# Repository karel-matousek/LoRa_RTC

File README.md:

# LoRa_RTC
This project is a Bachelor's thesis in progress, which pertains to the development and design of a LoRaWAN Class-B beacon receiver. The goal of the device is to extract and decode the time information contained in the received message, display it using an OLED display, and generate a 1pps output signal.

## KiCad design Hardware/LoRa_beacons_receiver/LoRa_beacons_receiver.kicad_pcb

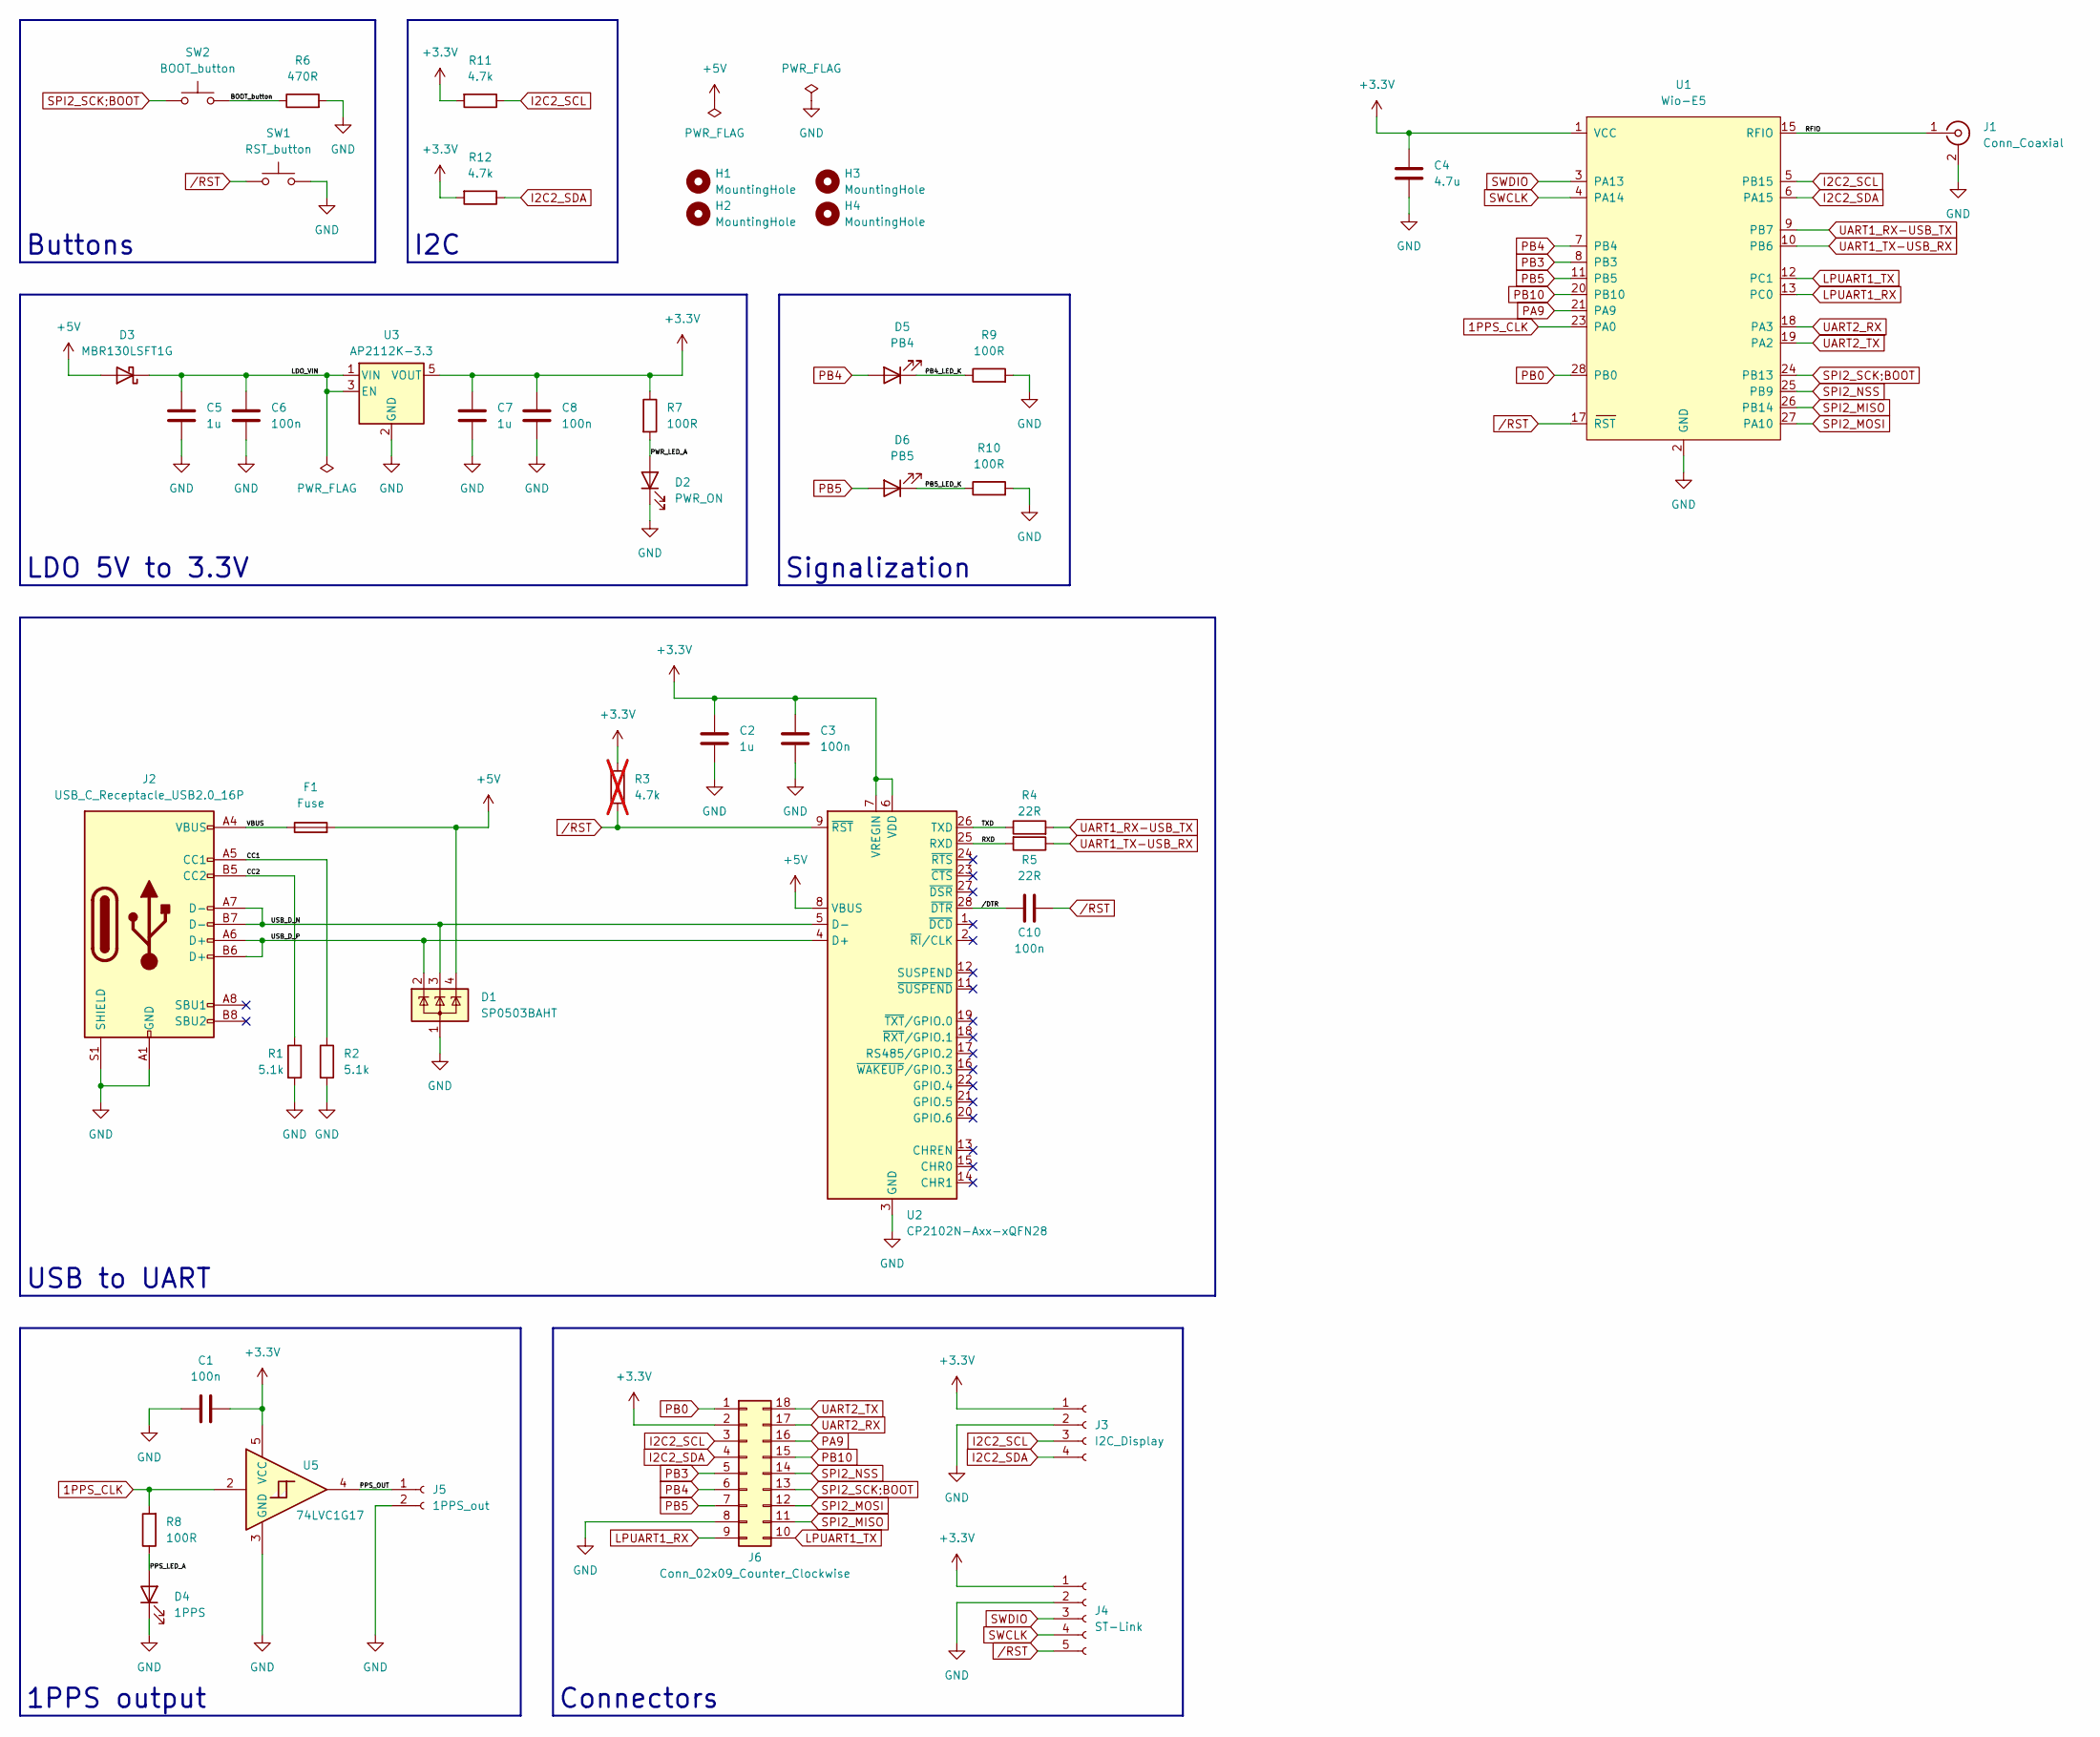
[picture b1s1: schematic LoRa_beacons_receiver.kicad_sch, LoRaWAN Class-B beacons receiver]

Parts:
C1, C3, C6, C8, C10: 100n; C_0805_2012Metric_Pad1.18x1.45mm_HandSolder; Manufacturer part number 08055C104JAT2A
C2, C5, C7: 1u; C_0805_2012Metric_Pad1.18x1.45mm_HandSolder; Manufacturer part number CC0805KKX7R7BB105
C4: 4.7u; C_0805_2012Metric_Pad1.18x1.45mm_HandSolder; Manufacturer part number TMK212AB7475KG-T
D1: SP0503BAHT; SOT-143; Manufacturer part number SP0503BAHTG-LF
D2: PWR_ON; LED_0805_2012Metric_Pad1.15x1.40mm_HandSolder; Manufacturer part number LTST-C171KRKT
D3: MBR130LSFT1G; SOD-123FL_l; Manufacturer part number MBR130LSFT1G
D4: 1PPS; LED_0805_2012Metric_Pad1.15x1.40mm_HandSolder; Manufacturer part number LTST-C171KRKT
D5: PB4; LED_0805_2012Metric_Pad1.15x1.40mm_HandSolder; Manufacturer part number LTST-C171KRKT
D6: PB5; LED_0805_2012Metric_Pad1.15x1.40mm_HandSolder; Manufacturer part number LTST-C171KRKT
F1: Fuse; Fuse_0603_1608Metric_Pad1.05x0.95mm_HandSolder; Manufacturer part number ERBRE1R00V
H1, H2, H3, H4: MountingHole; MountingHole_2.2mm_M2
J1: Conn_Coaxial; RF2-143-T-17-50-G_l; Manufacturer part number RF2-143-T-17-50-G
J2: USB_C_Receptacle_USB2.0_16P; USB_C_Receptacle_GCT_USB4105-xx-A_16P_TopMnt_Horizontal; Manufacturer part number USB4105-GF-A-120
J3: I2C_Display; PinSocket_1x04_P2.54mm_Vertical
J4: ST-Link; PinSocket_1x05_P2.54mm_Vertical; Manufacturer part number ZL262-5SG
J5: 1PPS_out; PinSocket_1x02_P2.54mm_Horizontal; Manufacturer part number ZL263-2SG
J6: Conn_02x09_Counter_Clockwise; PinSocket_2x09_P2.54mm_Vertical; Manufacturer part number ZL262-9SG
R1, R2: 5.1k; R_0805_2012Metric_Pad1.20x1.40mm_HandSolder; Manufacturer part number WR08X5101FTL
R3: 4.7k; R_0805_2012Metric_Pad1.20x1.40mm_HandSolder; Manufacturer part number CRCW08054K70FKTABC; not fitted
R4, R5: 22R; R_0805_2012Metric_Pad1.20x1.40mm_HandSolder; Manufacturer part number CRGH0805J22R
R6: 470R; R_0805_2012Metric_Pad1.20x1.40mm_HandSolder; Manufacturer part number ERJP06J471V
R7, R8, R9, R10: 100R; R_0805_2012Metric_Pad1.20x1.40mm_HandSolder; Manufacturer part number CRCW0805100RFKTABC
R11, R12: 4.7k; R_0805_2012Metric_Pad1.20x1.40mm_HandSolder; Manufacturer part number CRCW08054K70FKTABC
SW1: RST_button; SW_PUSH_6mm; Manufacturer part number TACT4101-11250-A
SW2: BOOT_button; SW_PUSH_6mm; Manufacturer part number TACT4101-11250-A
U1: Wio-E5; STM32WLE5JC_l
U2: CP2102N-Axx-xQFN28; QFN-28-1EP_5x5mm_P0.5mm_EP3.35x3.35mm; Manufacturer part number CP2102-GM
U3: AP2112K-3.3; SOT-23-5; Manufacturer part number AP2112K-3.3TRG1
U5: 74LVC1G17; SOT-23-5_HandSoldering; Manufacturer part number 74LVC1G17GV.125

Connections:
1PPS_CLK: R8.2, U1.23 (PA0), U5.2
+3.3V: C1.1, C2.1, C3.1, C4.1, C7.1, C8.1, J3.1, J4.1, J6.2, R3.1, R7.1, R11.2, R12.2, U1.1 (VCC), U2.6 (VDD), U2.7 (VREGIN), U3.5 (VOUT), U5.5 (VCC)
+5V: D1.4 (K), D3.2 (A), F1.2, U2.8 (VBUS)
/BOOT_button: R6.1, SW2.2
/CC1: J2.A5 (CC1), R2.1
/CC2: J2.B5 (CC2), R1.1
/LDO_VIN: C5.1, C6.1, D3.1 (K), U3.1 (VIN), U3.3 (EN)
/PB4_LED_K: D5.1 (K), R9.1
/PB5_LED_K: D6.1 (K), R10.1
/PPS_LED_A: D4.2 (A), R8.1
/PPS_OUT: J5.1, U5.4
/PWR_LED_A: D2.2 (A), R7.2
/RFIO: J1.1 (In), U1.15 (RFIO)
/RXD: R5.2, U2.25 (RXD)
/TXD: R4.1, U2.26 (TXD)
/USB_D_N: D1.3 (K), J2.A7 (D-), J2.B7 (D-), U2.5 (D-)
/USB_D_P: D1.2 (K), J2.A6 (D+), J2.B6 (D+), U2.4 (D+)
/VBUS: F1.1, J2.A4 (VBUS), J2.A9 (VBUS), J2.B4 (VBUS), J2.B9 (VBUS)
//DTR: C10.1, U2.28 (~DTR)
GND: C1.2, C2.2, C3.2, C4.2, C5.2, C6.2, C7.2, C8.2, D1.1 (A), D2.1 (K), D4.1 (K), J1.2 (Ext), J2.A1 (GND), J2.A12 (GND), J2.B1 (GND), J2.B12 (GND), J2.S1 (SHIELD), J3.2, J4.2, J5.2, J6.8, R1.2, R2.2, R6.2, R9.2, R10.2, SW1.2, U1.2 (GND), U1.14 (GND), U1.16 (GND), U1.22 (GND), U2.3 (GND), U2.29 (GND), U3.2 (GND), U5.3 (GND)
I2C2_SCL: J3.3, J6.3, R11.1, U1.5 (PB15)
I2C2_SDA: J3.4, J6.4, R12.1, U1.6 (PA15)
LPUART1_RX: J6.9, U1.13 (PC0)
LPUART1_TX: J6.10, U1.12 (PC1)
PA9: J6.16, U1.21 (PA9)
PB0: J6.1, U1.28 (PB0)
PB3: J6.5, U1.8 (PB3)
PB4: D5.2 (A), J6.6, U1.7 (PB4)
PB5: D6.2 (A), J6.7, U1.11 (PB5)
PB10: J6.15, U1.20 (PB10)
SPI2_MISO: J6.11, U1.26 (PB14)
SPI2_MOSI: J6.12, U1.27 (PA10)
SPI2_NSS: J6.14, U1.25 (PB9)
SPI2_SCK;BOOT: J6.13, SW2.1, U1.24 (PB13~)
SWCLK: J4.4, U1.4 (PA14)
SWDIO: J4.3, U1.3 (PA13)
UART1_RX-USB_TX: R4.2, U1.9 (PB7)
UART1_TX-USB_RX: R5.1, U1.10 (PB6)
UART2_RX: J6.17, U1.18 (PA3)
UART2_TX: J6.18, U1.19 (PA2)
/RST: C10.2, J4.5, R3.2, SW1.1, U1.17 (RST), U2.9 (~RST)

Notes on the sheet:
LDO 5V to 3.3V
Connectors
USB to UART
1PPS output
Signalization
Buttons
I2C

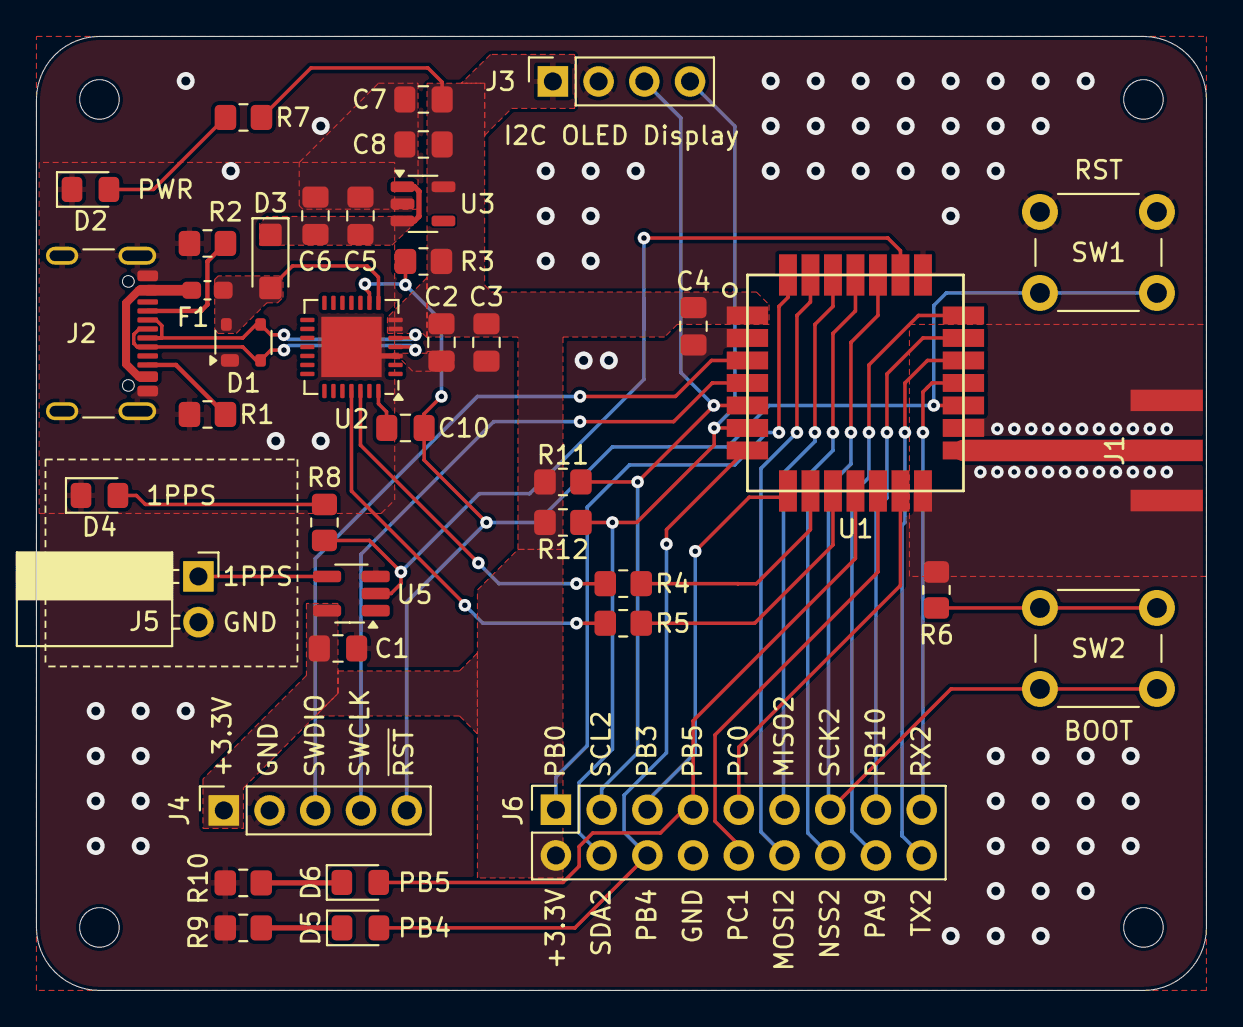
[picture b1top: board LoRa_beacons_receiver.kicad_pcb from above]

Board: 2 copper layers, 65.0 x 53.0 mm, 44 parts (0 on the bottom side), 41 nets.

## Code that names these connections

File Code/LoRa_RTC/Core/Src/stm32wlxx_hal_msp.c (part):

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    __HAL_RCC_GPIOA_CLK_ENABLE();
    __HAL_RCC_GPIOB_CLK_ENABLE();
    /**I2C2 GPIO Configuration
    PA15     ------> I2C2_SDA
    PB15     ------> I2C2_SCL
    */
    GPIO_InitStruct.Pin = GPIO_PIN_15;
    GPIO_InitStruct.Mode = GPIO_MODE_AF_OD;
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    __HAL_RCC_I2C2_CLK_DISABLE();

    /**I2C2 GPIO Configuration
    PA15     ------> I2C2_SDA
    PB15     ------> I2C2_SCL
    */
    HAL_GPIO_DeInit(GPIOA, GPIO_PIN_15);

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
    __HAL_RCC_GPIOA_CLK_ENABLE();
    /**TIM2 GPIO Configuration
    PA0     ------> TIM2_CH1
    */
    GPIO_InitStruct.Pin = GPIO_PIN_0;
    GPIO_InitStruct.Mode = GPIO_MODE_AF_PP;
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
    __HAL_RCC_GPIOB_CLK_ENABLE();
    /**USART1 GPIO Configuration
    PB7     ------> USART1_RX
    PB6     ------> USART1_TX
    */
    GPIO_InitStruct.Pin = GPIO_PIN_7|GPIO_PIN_6;
    GPIO_InitStruct.Mode = GPIO_MODE_AF_PP;
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    __HAL_RCC_USART1_CLK_DISABLE();

    /**USART1 GPIO Configuration
    PB7     ------> USART1_RX
    PB6     ------> USART1_TX
    */
    HAL_GPIO_DeInit(GPIOB, GPIO_PIN_7|GPIO_PIN_6);

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
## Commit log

2025-09-28 Git test
2025-10-04 Core of the code
2025-11-07 First version, waiting for testing
2025-11-11 First functional version
2025-12-17 Added OLED display
2025-12-17 Cleanup: deleted of the folder Debug/ from git
2026-01-01 Minor changes, OLED configuration
2026-02-15 gitignore update for KiCAD; added KiCAD schematic of the device
2026-02-15 First complete schematic version
2026-02-15 Minor schematic adjustments; first version of PCB layout
2026-02-20 Recommended KiCAD changes; PCB layout changes
2026-02-21 Clenaup
2026-02-23 Minor schematic changes
2026-02-26 Minor schematic changes; PCB WIP
2026-02-28 First version of completely routed PCB
2026-03-02 Minor changes
2026-03-03 Recommended changes
2026-03-06 Minor PCB changes
2026-03-24 fix: repetitive beacon reception; basic 1PPS (WIP); hw: final changes before PSB order
2026-05-05 SW: Added time and date formatting; SW: First version of timer regulation; HW: Created ibom
2026-05-20 SW: PI regulator implementation; bug fixes
2026-05-22 SW:WIP - PI regulator
2026-05-22 SW:WIP PI regulator with TIM16
2026-05-29 SW: functional regulation; HW: schematic shrink
2026-05-30 SW:Regulation WIP
2026-05-30 SW:WIP
2026-05-31 SW: Regulation modification
2026-06-01 SW: cleanup
2026-06-14 cleanup

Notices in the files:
Code/LoRa_RTC/Core/Src/stm32wlxx_hal_msp.c:
Copyright (c) 2025 STMicroelectronics.
All rights reserved.
This software is licensed under terms that can be found in the LICENSE file
